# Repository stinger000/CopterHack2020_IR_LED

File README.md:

# CopterHack2020_IR_LED
The main repository of the team "Atomic Ferrets" in the competition CopterHack 2020

## Описание проекта

- Проект представляет собой систему инфракрасной засечки, которая устанавливается на ворота или любое другое препятствие на трассе, и позволяет фиксировать факт пролёта дроном определенного элемента трассы, а также засекать время пролёта. Данная система позволит максимально автоматизировать проведение любых соревнований, связанных с беспилотным спортом. Так, участнику будет достаточно просто запустить дрон, после чего вылет будет оценен автоматически, в соответствии с заданными критериями. Это позволит исключить возможность судейской ошибки и позволит оценивать проведение любых чемпионатов максимально объективно.

## Каким мы видим результат проекта?

- Проект будет представлен в виде системы инфракрасных датчиков, которые крепятся к препятствиям трассы, а также базовой станции, которая принимает и обрабатывает сигнал с этих датчиков. Датчики могут подключаться последовательно, что позволит устанавливать их на элементы трассы любого размера. В базовых станциях будет реализована возможность их объединения в единую сеть посредствам беспроводного интерфейса, что позволит засекать прохождение любого количества элементов трассы. Также, в рамках проекта будет реализовано приложение для мобильного телефона и ПК, которое будет принимать сигнал с базовых станций, позволит задавать конфигурацию трассы, критерии оценки, и по окончанию вылета выдавать оценку в автоматическом режиме.

## Клевер

- Клевер сейчас является одной из самых популярных платформ для проведения беспилотных соревнований. Разрабатывая нашу систему засечки мы в первую очередь ориентируемся на соревнования с участием этого дрона. Хотя стоит сказать, что использовать устройство можно на любых других соревнованиях. Также ее может использовать любой желающий подготовиться к соревнованиям либо в других личных целях. Конечный вид сборки устройства и установки софта предполагает простоту в использовании

## Место продукта на рынке

- Наша версия системы засечки предполагает, что на дрон не придется ставить дополнительное оборудование, которое будет увеличивать его вес ( максимум - это один светодиод, который позволит определять какой имеено дрон пролетает. Этот вариант еще не реализован ). Многие системы засечек предлагают При этом полный комплект оборудования с реализованным на нём ПО предполагает невысокую стоимость. Конечного продукта нет, поэтому и точной цены тоже, но мы хотим сделать продукт доступным в цене, и опираемся на эту идею при разработке. 

## Стадия разработки
- **Видео** с проверкой работоспособности проекта можете посмотреть по ссылке https://youtu.be/BEOIffvngIY
- Засечка осуществляется за счет фотодиода, реагирующего на свет. Измерения осуществляются путем срабатывания системы на светодиод, закрепленный на противоположной стороне ворот соосно системе срабатывания. 
- Сейчас у нас есть электронная схема, позволяющая снять данные с фотодиода для последующей ее обработки. 
 
- Разработана электронная схема для засечки. 
- Создан алгоритм обработки сигнала с засечки
- Создается софт для ПК с интерфейсом наблюдения замеров времени. https://github.com/stinger000/CopterHack2020_IR_LED_Desktop_GUI
- Была реализована тестовая модель засечки, на которой было проверено срабатывание системы на светодиод, и она оказалась рабочей. 
- Есть система передачи видео с дрона через интернет в любую точку планеты
- Идёт процесс создания мобильного приложения для отслеживания замеров
 
 ### Дальнейшие планы 
- разработать приложение для конечного пользователя на PC и Android
- создать корпус для системы, позволяющий ей правильно работать в полевых условиях (закреплен на препятствие и правильно реагирует на пролет дрона) 

   Возможно рассмотрение некоторых вариантов реализации 
- **Идентификация дронов по частоте мигания светодиода**. Если на квадракоптеры установить по одному светодиоду, и сделать так, чтобы они мигали с индивидуальной для каждого  дрона частотой, то таким образом можно попытаться различить, кто и когда пролетел через препятствие, анализируя полученные сигналы.
- **Идентификация дронов с помощью камер и меток.** В интернете реализован проект система засечки, использующий только камеры самих дронов и передатчики видео. В этом проекте на контрольных точках устанавливается множество aruco-меток, с помощью которых фиксирует время прохождения этих точек. Мы хотим использовать этот проект, таким образом объединив 2 решения. Нашу систему, которая точно определяет время каждого пролета, но пока не может определить кто их соверишл. И систему, которая с неизвестной точностью, но определяет время пролета и id гонщика.

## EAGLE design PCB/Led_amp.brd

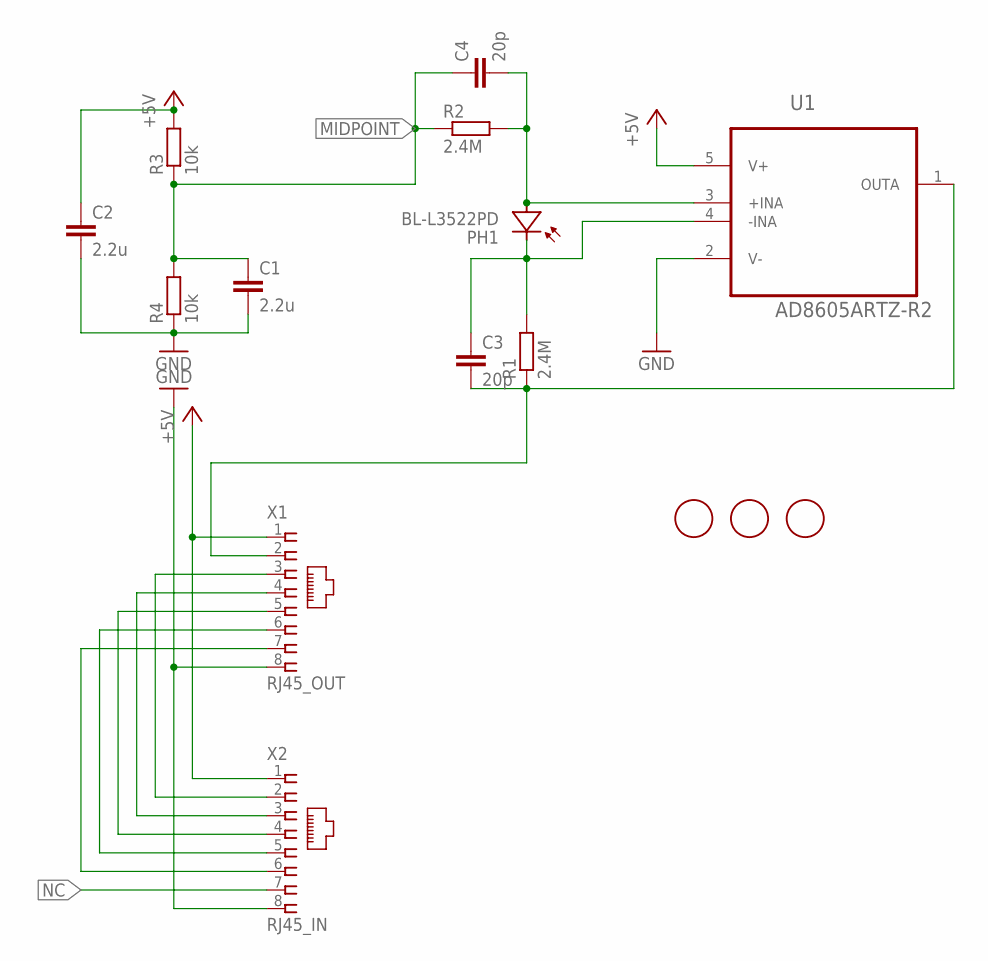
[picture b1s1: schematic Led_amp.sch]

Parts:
C1, C2: 2.2u; C0805
C3, C4: 20p; C0805
PH1: BL-L3522PD; PDOTODIODE_RECT
R1, R2: 2.4M; R0805
R3, R4: 10k; R0805
U1: AD8605ARTZ-R2; SOT95P290X145-5N
U$1, U$2, U$3: FIDUCIALLARGE_1MM; FIDUCIAL_1MM_LARGE
X1: RJ45_OUT; DS1134
X2: RJ45_IN; DS1134

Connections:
+5V: C2.1, R3.2, U1.5 (V+), X1.1, X2.1
GND: C1.2, C2.2, R4.1, U1.2 (V-), X1.8, X2.8
IN+: C4.2, PH1.A, R2.2, U1.3 (+INA)
IN-: C3.1, PH1.K (C), R1.2, U1.4 (-INA)
MIDPOINT: C1.1, C4.1, R2.1, R3.1, R4.2
NC: X2.7
OUT: C3.2, R1.1, U1.1 (OUTA), X1.2
OUT2: X1.3, X2.2
OUT3: X1.4, X2.3
OUT4: X1.5, X2.4
OUT5: X1.6, X2.5
OUT6: X1.7, X2.6

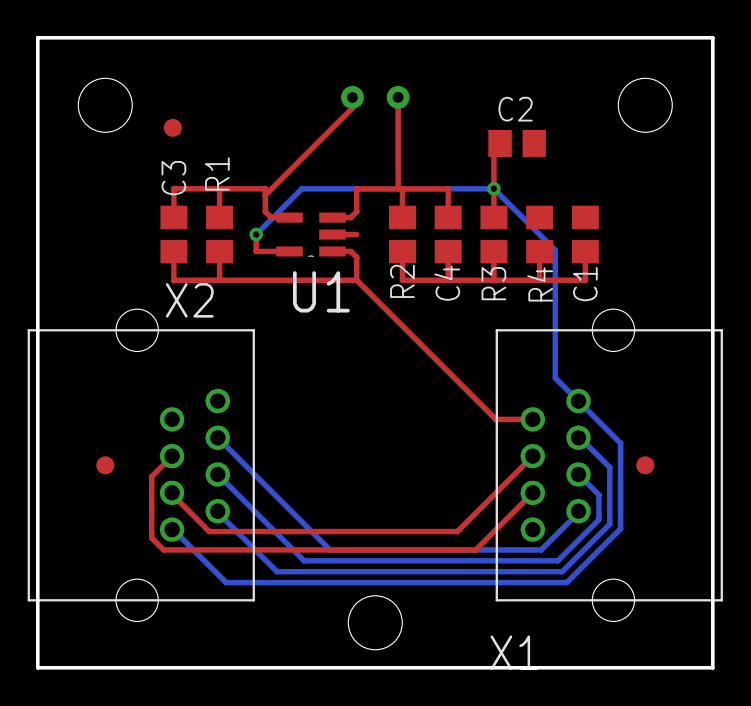
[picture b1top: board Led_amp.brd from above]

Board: 2 copper layers, 37.5 x 35.0 mm, 15 parts (1 on the bottom side), 11 nets.

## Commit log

2020-10-01 Add short description
2020-10-01 add 3d-models
2020-10-01 create folder for code
2020-10-01 Add schematic and PCB
2020-10-31 Update of october
2020-10-31 Add plans
2020-10-31 add video
2021-03-16 update signal handle
